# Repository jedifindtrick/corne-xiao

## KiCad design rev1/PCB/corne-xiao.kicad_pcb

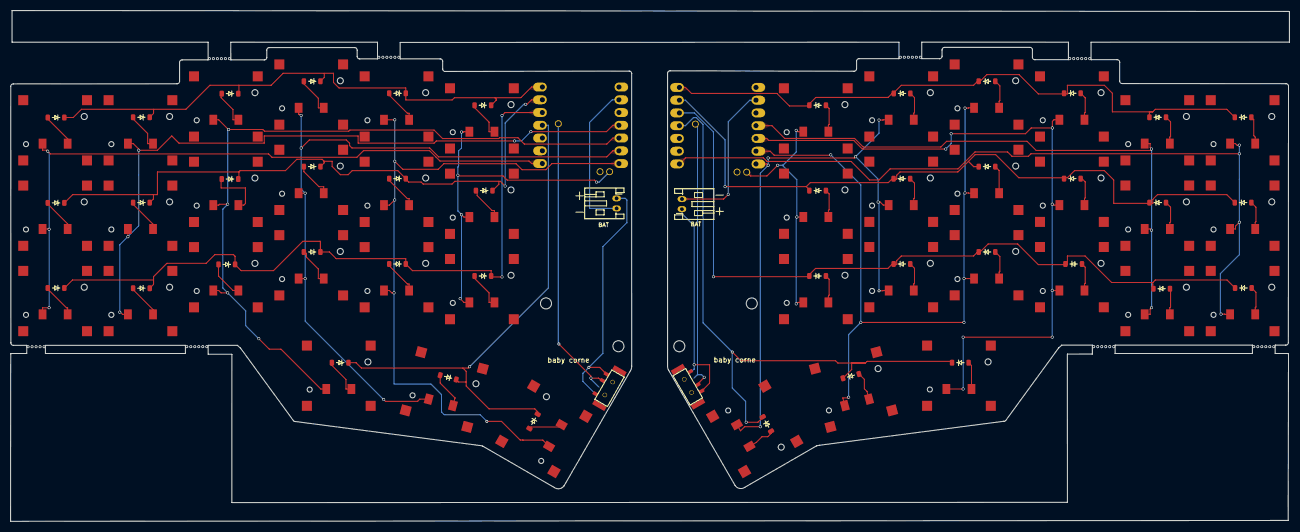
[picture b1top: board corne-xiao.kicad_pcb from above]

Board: 2 copper layers, 254.7 x 101.7 mm, 94 parts (0 on the bottom side), 68 nets.

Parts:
B1, B2: JST Battery; JST_PH_S2B-PH-K_1x02_P2.00mm_Horizontal
D1, D2, D3, D4, D5, D6, D7, D8, D9, D10, D11, D12, D13, D14, D15, D16, D17, D18, D19, D20, D21, D22, D23, D24, D25, D26, D27, D28, D29, D30, D31, D32, D33, D34, D35, D36, D37, D38, D39, D40, D41, D42: D; Diode_SOD-123
H6, H7, H13, H14: MountingHole; M2_HOLE_v2
PSW1, PSW2: SW_SPDT; MSK12C02_reversible
SW1, SW2, SW3, SW4, SW5, SW6, SW7, SW8, SW9, SW10, SW11, SW12, SW13, SW14, SW15, SW16, SW17, SW18, SW19, SW20, SW21, SW22, SW23, SW24, SW25, SW26, SW27, SW28, SW29, SW30, SW31, SW32, SW33, SW34, SW35, SW36, SW37, SW38, SW39, SW40, SW41, SW42: SW_PUSH; CPG1316S01D02_mikeholscher
U1, U2: xiao-ble; xiao-ble-tht

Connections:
BAT+_L: PSW1.2 (B), U1.15 (BAT)
BAT+_R: PSW2.2 (B), U2.15 (BAT)
COL0_L: SW1.1, SW7.1, SW13.1, U1.7 (B8_TX/1.11)
COL0_R: SW22.1, SW28.1, SW34.1, U2.7 (B8_TX/1.11)
COL1_L: SW2.1, SW8.1, SW14.1, U1.11 (A6_MOSI/1.15)
COL1_R: SW23.1, SW29.1, SW35.1, U2.11 (A6_MOSI/1.15)
COL2_L: SW3.1, SW9.1, SW15.1, SW19.1, U1.10 (A5_MISO/1.14)
COL2_R: SW24.1, SW30.1, SW36.1, SW40.1, U2.10 (A5_MISO/1.14)
COL3_L: SW4.1, SW10.1, SW16.1, SW20.1, U1.9 (A7_SCK/1.13)
COL3_R: SW25.1, SW31.1, SW37.1, SW41.1, U2.9 (A7_SCK/1.13)
COL4_L: SW5.1, SW11.1, SW17.1, SW21.1, U1.8 (B9_RX/1.12)
COL4_R: SW26.1, SW32.1, SW38.1, SW42.1, U2.8 (B9_RX/1.12)
COL5_L: SW6.1, SW12.1, SW18.1, U1.17 (NFC2/0.10_H)
COL5_R: SW27.1, SW33.1, SW39.1, U2.17 (NFC2/0.10_H)
GND: B1.2, U1.13 (GND)
GND1: B2.2, U2.13 (GND)
unnamed: D1.2 (A), SW1.2
unnamed: D2.2 (A), SW2.2
unnamed: D3.2 (A), SW3.2
unnamed: D4.2 (A), SW4.2
unnamed: D5.2 (A), SW5.2
unnamed: D6.2 (A), SW6.2
unnamed: D7.2 (A), SW7.2
unnamed: D8.2 (A), SW8.2
unnamed: D9.2 (A), SW9.2
unnamed: D10.2 (A), SW10.2
unnamed: D11.2 (A), SW11.2
unnamed: D12.2 (A), SW12.2
unnamed: D13.2 (A), SW13.2
unnamed: D14.2 (A), SW14.2
unnamed: D15.2 (A), SW15.2
unnamed: D16.2 (A), SW16.2
unnamed: D17.2 (A), SW17.2
unnamed: D18.2 (A), SW18.2
unnamed: D19.2 (A), SW19.2
unnamed: D20.2 (A), SW20.2
unnamed: D21.2 (A), SW21.2
unnamed: D22.2 (A), SW22.2
unnamed: D23.2 (A), SW23.2
unnamed: D24.2 (A), SW24.2
unnamed: D25.2 (A), SW25.2
unnamed: D26.2 (A), SW26.2
unnamed: D27.2 (A), SW27.2
unnamed: D28.2 (A), SW28.2
unnamed: D29.2 (A), SW29.2
unnamed: D30.2 (A), SW30.2
unnamed: D31.2 (A), SW31.2
unnamed: D32.2 (A), SW32.2
unnamed: D33.2 (A), SW33.2
unnamed: D34.2 (A), SW34.2
unnamed: D35.2 (A), SW35.2
unnamed: D36.2 (A), SW36.2
unnamed: D37.2 (A), SW37.2
unnamed: D38.2 (A), SW38.2
unnamed: D39.2 (A), SW39.2
unnamed: D40.2 (A), SW40.2
unnamed: D41.2 (A), SW41.2
unnamed: D42.2 (A), SW42.2
ROW0_L: D1.1 (K), D2.1 (K), D3.1 (K), D4.1 (K), D5.1 (K), D6.1 (K), U1.1 (A2/0.02_H)
ROW0_R: D22.1 (K), D23.1 (K), D24.1 (K), D25.1 (K), D26.1 (K), D27.1 (K), U2.1 (A2/0.02_H)
ROW1_L: D7.1 (K), D8.1 (K), D9.1 (K), D10.1 (K), D11.1 (K), D12.1 (K), U1.2 (A4/0.03_H)
ROW1_R: D28.1 (K), D29.1 (K), D30.1 (K), D31.1 (K), D32.1 (K), D33.1 (K), U2.2 (A4/0.03_H)
ROW2_L: D13.1 (K), D14.1 (K), D15.1 (K), D16.1 (K), D17.1 (K), D18.1 (K), U1.3 (A10/0.28)
ROW2_R: D34.1 (K), D35.1 (K), D36.1 (K), D37.1 (K), D38.1 (K), D39.1 (K), U2.3 (A10/0.28)
ROW3_L: D19.1 (K), D20.1 (K), D21.1 (K), U1.4 (A11/0.29)
ROW3_R: D40.1 (K), D41.1 (K), D42.1 (K), U2.4 (A11/0.29)
VBAT_L: B1.1, PSW1.3 (C)
VBAT_R: B2.1, PSW2.3 (C)

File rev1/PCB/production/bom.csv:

Designator,Footprint,Quantity,Value,LCSC Part #
"B1, B2",JST_PH_S2B-PH-K_1x02_P2.00mm_Horizontal,2,JST Battery,
"D1, D10, D11, D12, D13, D14, D15, D16, D17, D18, D19, D2, D20, D21, D22, D23, D24, D25, D26, D27, D28, D29, D3, D30, D31, D32, D33, D34, D35, D36, D37, D38, D39, D4, D40, D41, D42, D5, D6, D7, D8, D9",D3_SMD_v2,42,D,
"H13, H14, H6, H7",M2_HOLE_v2,4,MountingHole,
"PSW1, PSW2",MSK12C02_reversible,2,SW_SPDT,
"SW1, SW10, SW11, SW12, SW13, SW14, SW15, SW16, SW17, SW18, SW19, SW2, SW20, SW21, SW22, SW23, SW24, SW25, SW26, SW27, SW28, SW29, SW3, SW30, SW31, SW32, SW33, SW34, SW35, SW36, SW37, SW38, SW39, SW4, SW40, SW41, SW42, SW5, SW6, SW7, SW8, SW9",CPG1316S01D02_mikeholscher,42,SW_PUSH,
"U1, U2",xiao-ble-tht,2,xiao-ble,

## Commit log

2024-12-30 Start
2024-12-30 moar
2025-01-03 I forgot to backup.
2025-01-04 Backup
2025-01-05 again
2025-01-05 I don't care about the history of this repo.
